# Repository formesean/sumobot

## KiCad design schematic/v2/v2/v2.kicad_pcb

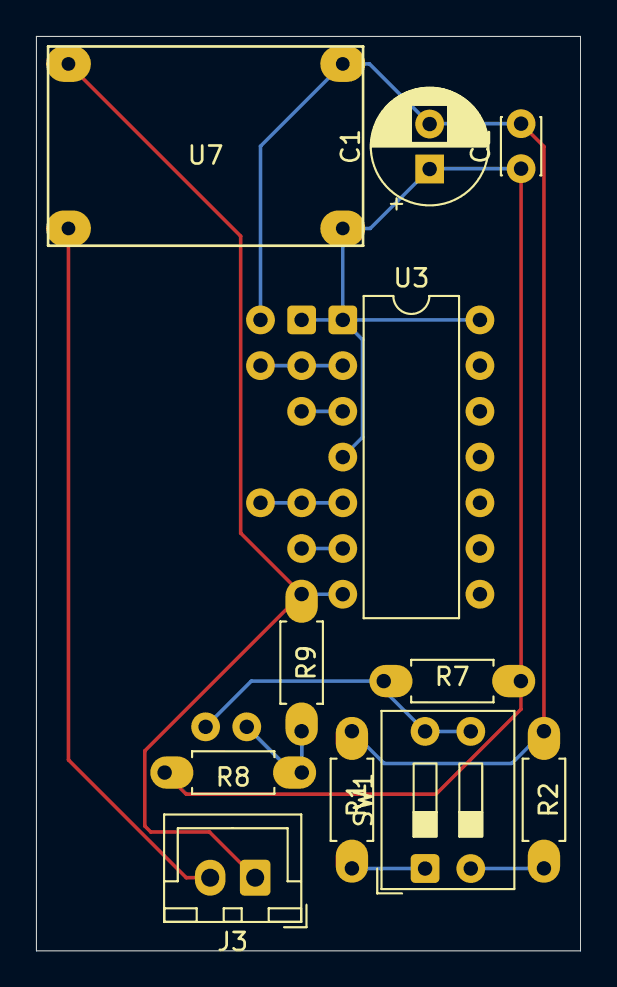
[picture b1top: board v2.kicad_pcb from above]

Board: 2 copper layers, 30.2 x 50.8 mm, 11 parts (0 on the bottom side), 7 nets.

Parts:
C1: 100uF; CP_Radial_D6.3mm_P2.50mm
C2: 0.1uF; C_Disc_D3.0mm_W2.0mm_P2.50mm
J3: Conn_01x02; JST_XH_B2B-XH-A_1x02_P2.50mm_Vertical
R1: 4.7k; R_Axial_DIN0207_L6.3mm_D2.5mm_P7.62mm_BIGPAD
R2, R7, R8: 10k; R_Axial_DIN0207_L6.3mm_D2.5mm_P7.62mm_BIGPAD
R9: 5.1k; R_Axial_DIN0207_L6.3mm_D2.5mm_P7.62mm_BIGPAD
SW1: SW_DIP_x02; SW_DIP_SPSTx02_Slide_9.78x7.26mm_W7.62mm_P2.54mm
U3: 74HC86; DIP-14_W7.62mm
U7: Mini360; Mini360_step-down

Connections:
/+5V_DC: C1.1, C2.1, R7.1, R8.1, U3.1, U3.4, U7.4 (OUT+)
/BATTERY_VOLTS: R8.2, R9.1
/STRATEGY_SWITCH: R7.2, SW1.3, SW1.4
/V_BATT: J3.2, U7.2 (IN+)
GND: C1.2, C2.2, J3.1, R1.2, R2.2, R9.2, U3.7, U7.1 (IN-), U7.3 (OUT-)
unnamed: R1.1, SW1.1
unnamed: R2.1, SW1.2

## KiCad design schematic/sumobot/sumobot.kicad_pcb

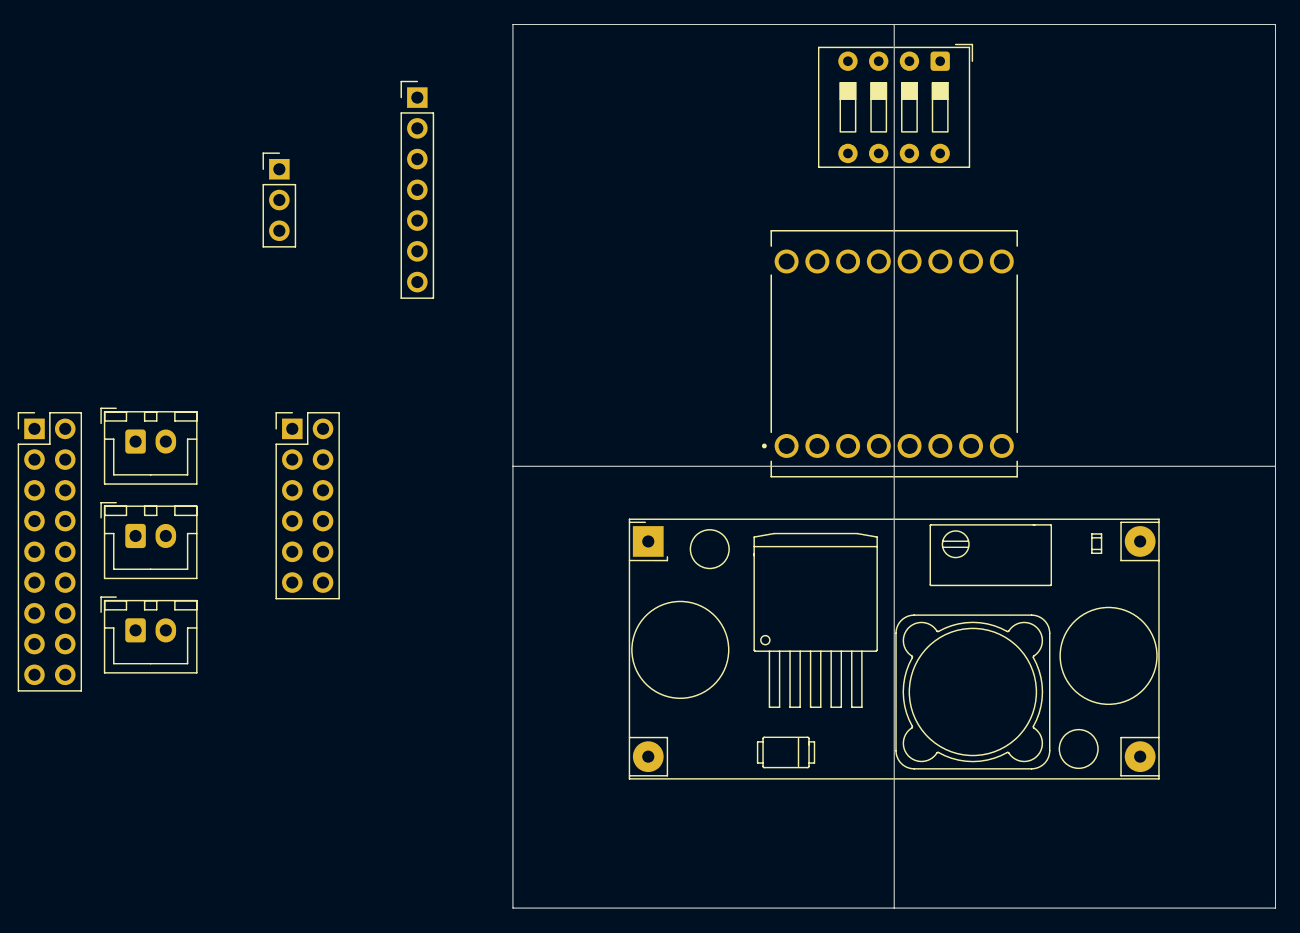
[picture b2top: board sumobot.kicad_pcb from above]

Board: 2 copper layers, 63.0 x 73.0 mm, 10 parts (0 on the bottom side), 21 nets, no tracks yet.

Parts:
J1: Conn_02x09_Odd_Even; PinHeader_2x09_P2.54mm_Vertical
J2: Conn_01x03; PinHeader_1x03_P2.54mm_Vertical
J3: Conn_02x06_Counter_Clockwise; PinHeader_2x06_P2.54mm_Vertical
J4, J5, J6: Conn_01x02_Socket; JST_XH_B2B-XH-A_1x02_P2.50mm_Vertical
J7: Conn_01x07; PinHeader_1x07_P2.54mm_Vertical
SW3: SW_DIP_x04; SW_DIP_SPSTx04_Slide_9.78x12.34mm_W7.62mm_P2.54mm
U1: ROB-14450; MODULE_ROB-14450
U2: YAAJ_DCDC_StepDown_LM2596

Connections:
+5V Batt: J1.1, J1.3, J1.5, J1.7, J1.9, J1.11, J1.13, J1.15, J1.17, U2.4 (Vout)
+12V Batt: J6.2, SW3.4
+12V Batt ON: SW3.5, U1.1 (VM), U2.1 (Vin)
-5V Batt: J1.2, J1.4, J1.6, J1.8, J1.10, J1.12, J1.14, J1.16, J1.18, U2.3 (GND)
-12V Batt: J6.1, SW3.1, SW3.2, SW3.3, U1.3 (GND), U1.8 (GND), U1.9 (GND), U2.2 (GND)
AI1: J7.3, U1.14 (AI1)
AI2: J7.2, U1.15 (AI2)
AO1: J4.1, U1.4 (A01)
AO2: J4.2, U1.5 (A02)
BI1: J7.5, U1.12 (BI1)
BI2: J7.6, U1.11 (BI2)
BIT0: J2.1, SW3.8
BIT1: J2.2, SW3.7
BIT2: J2.3, SW3.6
BO1: J5.2, U1.7 (B01)
BO2: J5.1, U1.6 (B02)
PWMA: J7.1, U1.16 (PWMA)
PWMB: J7.7, U1.10 (PWMB)
SCL: J3.2, J3.4, J3.6, J3.8, J3.10, J3.12
SDA: J3.1, J3.3, J3.5, J3.7, J3.9, J3.11
STBY: J7.4, U1.13 (STBY)

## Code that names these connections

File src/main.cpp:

#include <Arduino.h>
#include <Wire.h>
#include <driver/i2s.h>
#include "Adafruit_VL53L0X.h"
#include <IRrecv.h>
#include <IRremoteESP8266.h>
#include <IRutils.h>
#include "driver/adc.h"
#include "esp_adc_cal.h"

// Control
#define IR_REC_PIN 23
#define BIT1 9
#define BIT0 13

int strat = 0;
int strat_dir = 0;
bool stratExecuted = false;
bool setStrat = false;

// TB6612FNG
#define PWMA 32
#define AIN2 33
#define AIN1 25
#define STBY 26
#define BIN1 14
#define BIN2 27
#define PWMB 12
#define SPEED 128
#define MAX_SPEED 255
#define PWM_CHANNEL_A 0
#define PWM_CHANNEL_B 1
#define PWM_FREQ 16000
#define PWM_RESOLUTION 8

// VL53L0X
#define LOX1_ADDRESS 0x30
#define LOX2_ADDRESS 0x31
#define LOX3_ADDRESS 0x32
#define LOX4_ADDRESS 0x33
#define SHT_LOX1 19
#define SHT_LOX2 18
#define SHT_LOX3 17
#define SHT_LOX4 16

Adafruit_VL53L0X lox1, lox2, lox3, lox4;
VL53L0X_RangingMeasurementData_t measures[4];
Adafruit_VL53L0X *sensors[] = {&lox1, &lox2, &lox3, &lox4};

// Enums and Function Prototype

enum Direction
{
  FORWARD,
  BACKWARD,
  LEFT,
  RIGHT
};

void strategy(int strat);
void setMotorPWM(int speedA, int speedB);
void setMotorPins(bool ain1, bool ain2, bool bin1, bool bin2);
void motors(int speed, Direction direction, int delay_ms);
void triggerStrategyAdjustment();

void setup()
{
  Serial.begin(115200);
  Wire.begin();
  Wire.setClock(600000);

  // ADC1 Setup
  adc1_config_width(ADC_WIDTH_BIT_12);
  adc1_config_channel_atten(ADC1_CHANNEL_6, ADC_ATTEN_DB_12);
  adc1_config_channel_atten(ADC1_CHANNEL_7, ADC_ATTEN_DB_12);

  // Control Setup
  pinMode(2, OUTPUT);
  pinMode(IR_REC_PIN, INPUT);

  pinMode(BIT0, INPUT_PULLUP);
  pinMode(BIT1, INPUT_PULLUP);

  // VL53L0X Setup
  pinMode(SHT_LOX1, OUTPUT);
  pinMode(SHT_LOX2, OUTPUT);
  pinMode(SHT_LOX3, OUTPUT);
  pinMode(SHT_LOX4, OUTPUT);

  digitalWrite(SHT_LOX1, LOW);
  digitalWrite(SHT_LOX2, LOW);
  digitalWrite(SHT_LOX3, LOW);
  digitalWrite(SHT_LOX4, LOW);
  delay(10);

  digitalWrite(SHT_LOX1, HIGH);
  lox1.begin(LOX1_ADDRESS);

  digitalWrite(SHT_LOX2, HIGH);
  lox2.begin(LOX2_ADDRESS);

  digitalWrite(SHT_LOX3, HIGH);
  lox3.begin(LOX3_ADDRESS);

  digitalWrite(SHT_LOX4, HIGH);
  lox4.begin(LOX4_ADDRESS);

  for (auto sensor : sensors)
    sensor->setMeasurementTimingBudgetMicroSeconds(25000);

  // TB6612FNG Setup
  pinMode(AIN1, OUTPUT);
  pinMode(AIN2, OUTPUT);
  pinMode(BIN1, OUTPUT);
  pinMode(BIN2, OUTPUT);
  pinMode(STBY, OUTPUT);

  ledcSetup(PWM_CHANNEL_A, PWM_FREQ, PWM_RESOLUTION);
  ledcSetup(PWM_CHANNEL_B, PWM_FREQ, PWM_RESOLUTION);

  ledcAttachPin(PWMA, PWM_CHANNEL_A);
  ledcAttachPin(PWMB, PWM_CHANNEL_B);

  digitalWrite(STBY, HIGH);
}

void loop()
{
  bool start_button = digitalRead(IR_REC_PIN);

  if (!setStrat)
  {
    digitalWrite(2, HIGH);

    strat = ((!digitalRead(BIT1)) << 1) | (!digitalRead(BIT0));
    // Serial.printf("strat: %d\n", strat);

    sensors[0]->rangingTest(&measures[0], false);
    sensors[3]->rangingTest(&measures[3], false);

    if (measures[0].RangeMilliMeter < 100)
    {
      strat_dir--;
      triggerStrategyAdjustment();
    }
    if (measures[3].RangeMilliMeter < 100)
    {
      strat_dir++;
      triggerStrategyAdjustment();
    }
  }

  while (start_button == LOW)
  {
    digitalWrite(2, HIGH);

    if (!stratExecuted)
    {
      strategy(strat);
      stratExecuted = true;
    }

    uint16_t ir1_raw = adc1_get_raw(ADC1_CHANNEL_6);
    uint16_t ir2_raw = adc1_get_raw(ADC1_CHANNEL_7);

    // Serial.printf("IR1: %d\t\t IR2: %d\n", ir1_raw, ir2_raw);

    for (uint8_t i = 0; i < 4; i++)
      sensors[i]->rangingTest(&measures[i], false);

    // Serial.printf("1: %dmm\t\t2: %dmm\t\t3: %dmm\t\t4: %dmm\n",
    //               measures[0].RangeMilliMeter,
    //               measures[1].RangeMilliMeter,
    //               measures[2].RangeMilliMeter,
    //               measures[3].RangeMilliMeter);

    // motors(0, FORWARD, 0);

    if (ir1_raw > 250 && ir2_raw > 250)
    {
      if (measures[1].RangeMilliMeter < 200 && measures[2].RangeMilliMeter < 200)
        motors(MAX_SPEED, FORWARD, 0);
      else if (measures[0].RangeMilliMeter < 650)
        motors(MAX_SPEED, LEFT, 0);
      else if (measures[3].RangeMilliMeter < 650)
        motors(MAX_SPEED, RIGHT, 0);
      else
        motors(70, FORWARD, 0);
    }
    else
    {
      motors(MAX_SPEED, BACKWARD, 350);
      motors(MAX_SPEED, LEFT, 300);
    }
  }
}

void strategy(int strat)
{
  switch (strat)
  {
  case 0:
    if (strat_dir > 0)
      motors(MAX_SPEED, FORWARD, 500);
    break;

  case 1:
    // palikod
    if (strat_dir < 0)
      motors(MAX_SPEED, LEFT, 380);
    if (strat_dir > 0)
      motors(MAX_SPEED, RIGHT, 380);
    break;

  case 2:
    // pakilid
    if (strat_dir < 0)
      motors(MAX_SPEED, LEFT, 150);
    if (strat_dir > 0)
      motors(MAX_SPEED, RIGHT, 150);
    break;

  case 3:
    // pacurve
    if (strat_dir < 0)
    {
      motors(MAX_SPEED, LEFT, 190);
      setMotorPWM(MAX_SPEED * .70, MAX_SPEED * .55);
      setMotorPins(HIGH, LOW, LOW, HIGH);
      delay(900);
      motors(MAX_SPEED, RIGHT, 230);
    }
    if (strat_dir > 0)
    {
      motors(MAX_SPEED, RIGHT, 190);
      setMotorPWM(MAX_SPEED * .50, MAX_SPEED * .70);
      setMotorPins(HIGH, LOW, LOW, HIGH);
      delay(900);
      motors(MAX_SPEED, LEFT, 230);
    }
    break;
  }
}

void setMotorPWM(int speedA, int speedB)
{
  ledcWrite(PWM_CHANNEL_A, speedA);
  ledcWrite(PWM_CHANNEL_B, speedB);
}

void setMotorPins(bool ain2, bool ain1, bool bin1, bool bin2)
{
  digitalWrite(AIN2, ain2);
  digitalWrite(AIN1, ain1);
  digitalWrite(BIN1, bin1);
  digitalWrite(BIN2, bin2);
}

void motors(int speed, Direction direction, int delay_ms)
{
  switch (direction)
  {
  case FORWARD:
    setMotorPWM(speed, speed);
    setMotorPins(HIGH, LOW, LOW, HIGH);
    break;

  case BACKWARD:
    setMotorPWM(speed, speed);
    setMotorPins(LOW, HIGH, HIGH, LOW);
    break;

  case LEFT:
    setMotorPWM(speed, speed * 0.50);
    setMotorPins(LOW, HIGH, LOW, HIGH);
    break;

  case RIGHT:
    setMotorPWM(speed * 0.50, speed);
    setMotorPins(HIGH, LOW, HIGH, LOW);
    break;
  }

  delay(delay_ms);
}

void triggerStrategyAdjustment()
{
  setStrat = true;
  digitalWrite(2, LOW);
  delay(150);
}

// EOF

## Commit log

2025-03-14 chore: update working directory
2025-03-14 feat: LED, Motors, ToFSensor lib
2025-03-16 chore: update .gitignore and platformio.ini for project structure and dependencies
2025-03-16 feat: enhance ToFSensor class with address handling and initialization improvements
2025-03-16 fix: update net names and add junctions in schematic and PCB for improved connectivity
2025-03-16 feat: add G-code and STL files for Mini Sumobot Size Checker model
2025-03-16 chore: update platformio.ini; delete unused files
2025-03-16 chore: update .gitignore to exclude G-code files and remove Mini Sumobot Size Checker.gcode
2025-03-16 feat: integrate Motors and ToFSensor functionality in main.cpp with updated setup and loop logic
2025-03-22 haha
2025-04-03 feat: add new 3D models and schematic
2025-04-03 refactor: migrate project to ESP32 platform; remove legacy LED, Motors, and ToFSensor libraries;
2025-04-10 feat: implement control logic for multiple sensors and strategies
2025-04-29 feat: enhance main control logic with new sensor integration and strategy adjustments
2025-04-30 feat: migrate project to Arduino Nano platform; update configuration and add main control logic for new sensors
2025-05-22 feat: add new 3D models and schematic libraries
2025-05-22 feat: implement ADC and sensor management for improved control logic; add configuration and logging capabilities
2025-05-25 feat: enhance sensor management and control logic; add strategy selection and emitter control functions
